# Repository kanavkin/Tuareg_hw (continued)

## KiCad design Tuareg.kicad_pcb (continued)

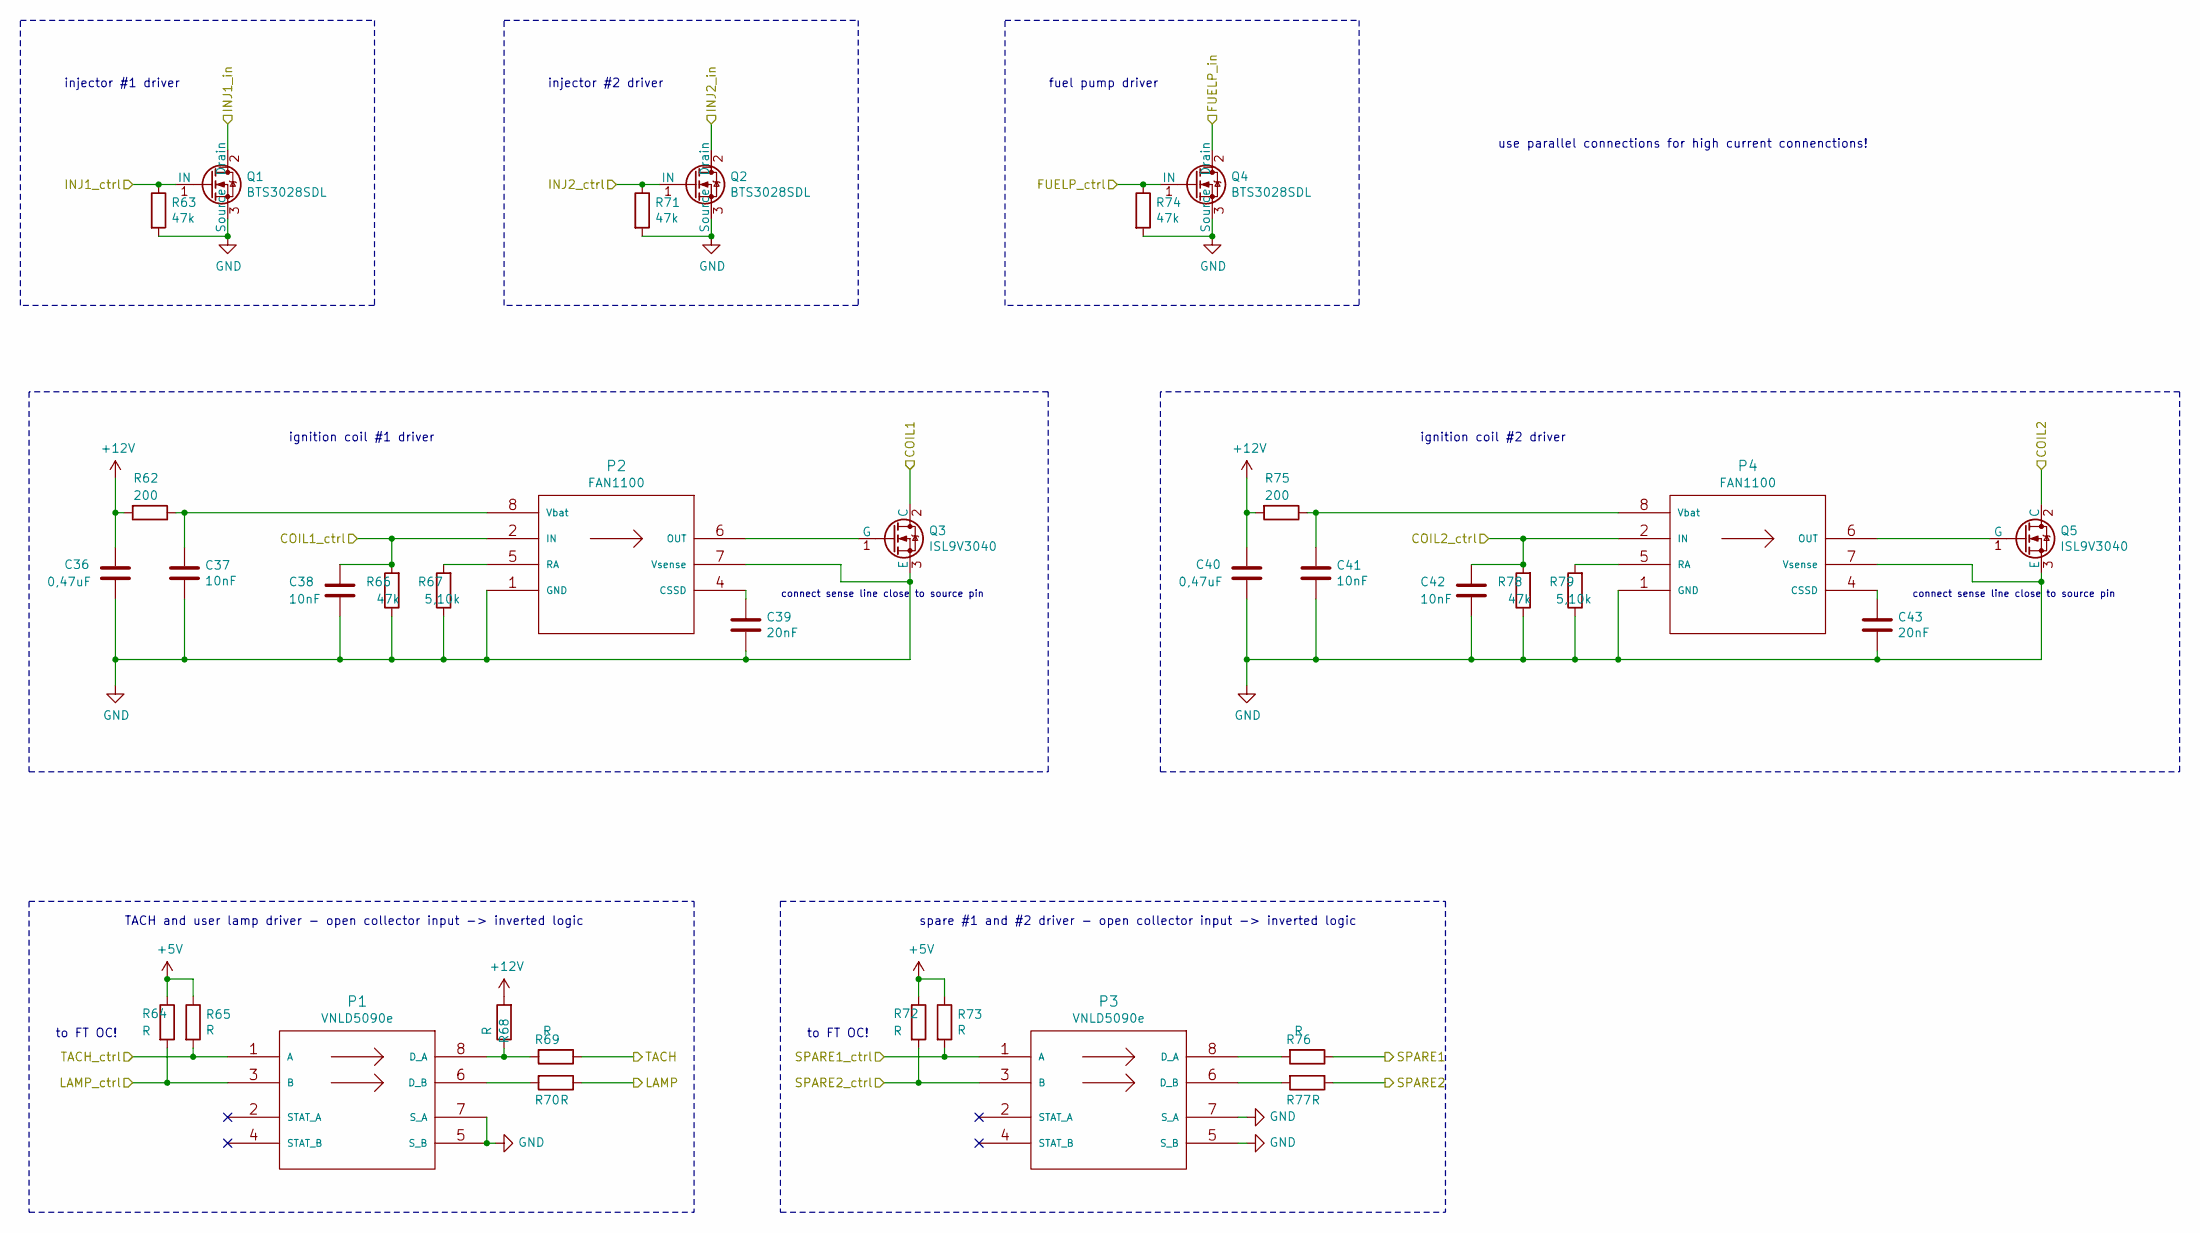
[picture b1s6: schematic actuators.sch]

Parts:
C36, C40: 0,47uF; C_0805_2012Metric
C37, C38, C41, C42: 10nF; C_0805_2012Metric
C39, C43: 20nF; C_0805_2012Metric
P1, P3: VNLD5090e
P2, P4: FAN1100; FAN_1100
Q1, Q2, Q4: BTS3028SDL; BTS3028SD
Q3, Q5: ISL9V3040
R62, R75: 200; R_1206_3216Metric
R63, R66, R71, R74, R78: 47k; R_0805_2012Metric
R64, R65, R68, R69, R70, R72, R73: R; R_0805_2012Metric
R67, R79: 5,10k; R_0805_2012Metric
R76, R77: R; R_1210_3225Metric

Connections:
+5V: R64.1, R65.1, R72.1, R73.1; also elsewhere on the board
+12V: C36.1, C40.1, R62.2, R68.2, R75.2; also elsewhere on the board
/COIL1: C38.1, P2.2 (IN), R66.2; also elsewhere on the board
/COIL2: C42.1, P4.2 (IN), R78.2; also elsewhere on the board
/FUELP: Q4.1 (IN), R74.1; also elsewhere on the board
/INJ1: Q1.1 (IN), R63.1; also elsewhere on the board
/INJ2: Q2.1 (IN), R71.1; also elsewhere on the board
/LAMP: P1.3 (B), R64.2; also elsewhere on the board
/TACH: P1.1 (A), R65.2; also elsewhere on the board
/con_coil1: Q3.2 (C); also elsewhere on the board
/con_coil2: Q5.2 (C); also elsewhere on the board
/con_fuelp: Q4.2 (Drain); also elsewhere on the board
/con_inj1: Q1.2 (Drain); also elsewhere on the board
/con_inj2: Q2.2 (Drain); also elsewhere on the board
/con_lamp: R70.1; also elsewhere on the board
/con_spareact1: R76.1; also elsewhere on the board
/con_spareact2: R77.1; also elsewhere on the board
/con_tach: R69.1; also elsewhere on the board
/spare_act_1: P3.1 (A), R73.2; also elsewhere on the board
/spare_act_2: P3.3 (B), R72.2; also elsewhere on the board
GND: C36.2, C37.2, C38.2, C39.2, C40.2, C41.2, C42.2, C43.2, P1.5 (S_B), P1.7 (S_A), P2.1 (GND), P2.7 (Vsense), P3.5 (S_B), P3.7 (S_A), P4.1 (GND), P4.7 (Vsense), Q1.3 (Source), Q2.3 (Source), Q3.3 (E), Q4.3 (Source), Q5.3 (E), R63.2, R66.1, R67.1, R71.2, R74.2, R78.1, R79.1; also elsewhere on the board
unnamed: C37.1, P2.8 (Vbat), R62.1
unnamed: C39.1, P2.4 (CSSD)
unnamed: C41.1, P4.8 (Vbat), R75.1
unnamed: C43.1, P4.4 (CSSD)
unnamed: P1.6 (D_B), R70.2
unnamed: P1.8 (D_A), R68.1, R69.2
unnamed: P2.5 (RA), R67.2
unnamed: P2.6 (OUT), Q3.1 (G)
unnamed: P3.6 (D_B), R77.2
unnamed: P3.8 (D_A), R76.2
unnamed: P4.5 (RA), R79.2
unnamed: P4.6 (OUT), Q5.1 (G)

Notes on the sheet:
injector #1 driver
injector #2 driver
fuel pump driver
ignition coil #1 driver
to FT OC!
TACH and user lamp driver - open collector input -> inverted logic
spare #1 and #2 driver - open collector input -> inverted logic
connect sense line close to source pin
ignition coil #2 driver
use parallel connections for high current connenctions!

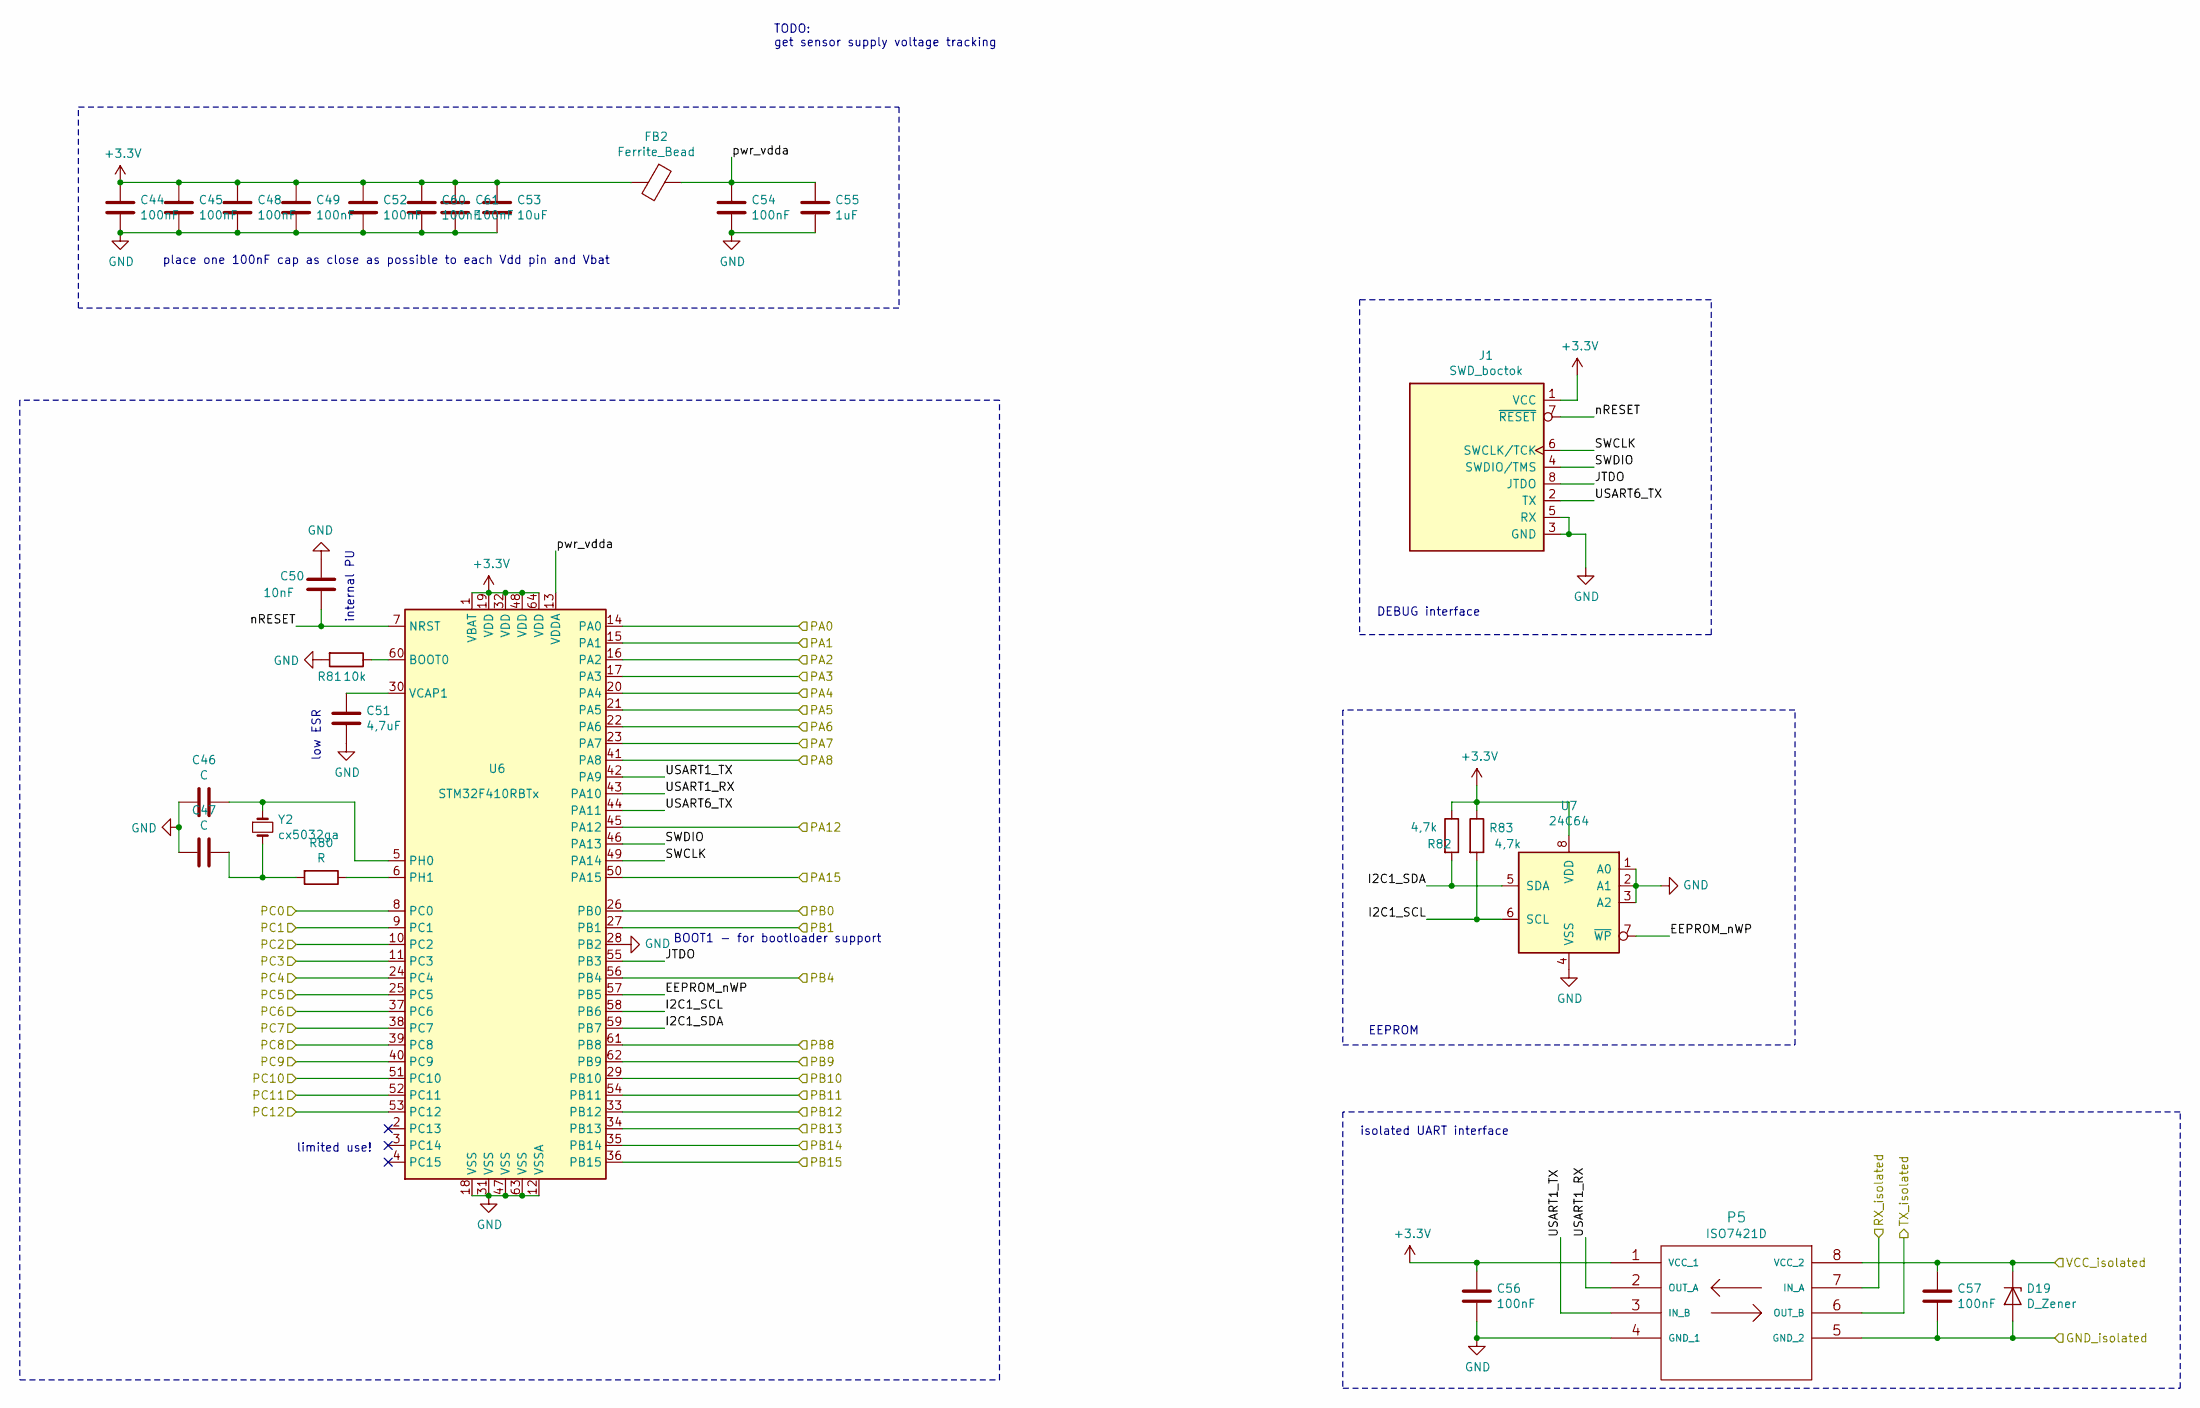
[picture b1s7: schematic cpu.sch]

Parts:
C44, C45, C48, C49, C52, C54, C56, C57, C60, C61: 100nF; C_0805_2012Metric
C46, C47: C; C_0805_2012Metric
C50: 10nF; C_0805_2012Metric
C51: 4,7uF; C_0805_2012Metric
C53: 10uF; C_1206_3216Metric
C55: 1uF; C_0805_2012Metric
D19: D_Zener; D_MELF
FB2: Ferrite_Bead; L_0805_2012Metric
J1: SWD_boctok; swd_boctok
P5: ISO7421D
R80: R; R_0805_2012Metric
R81: 10k; R_0805_2012Metric
R82, R83: 4,7k; R_0805_2012Metric
U6: STM32F410RBTx; LQFP-64_10x10mm_P0.5mm
U7: 24C64
Y2: cx5032ga; cx5032

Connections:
+3V3: C44.1, C45.1, C48.1, C49.1, C52.1, C53.1, C56.1, C60.1, C61.1, FB2.2, J1.1 (VCC), P5.1 (VCC_1), R82.1, R83.1, U6.1 (VBAT), U6.19 (VDD), U6.32 (VDD), U6.48 (VDD), U6.64 (VDD), U7.8 (VDD); also elsewhere on the board
/COIL1: U6.37 (PC6); also elsewhere on the board
/COIL2: U6.38 (PC7); also elsewhere on the board
/FUELP: U6.51 (PC10); also elsewhere on the board
/INJ1: U6.39 (PC8); also elsewhere on the board
/INJ2: U6.40 (PC9); also elsewhere on the board
/LAMP: U6.53 (PC12); also elsewhere on the board
/TACH: U6.52 (PC11); also elsewhere on the board
/ach1: U6.17 (PA3); also elsewhere on the board
/ach2: U6.16 (PA2); also elsewhere on the board
/ach3: U6.15 (PA1); also elsewhere on the board
/ach4: U6.14 (PA0); also elsewhere on the board
/ach5: U6.24 (PC4); also elsewhere on the board
/ach6: U6.23 (PA7); also elsewhere on the board
/ach8: U6.20 (PA4); also elsewhere on the board
/bat: U6.21 (PA5); also elsewhere on the board
/cam: U6.27 (PB1); also elsewhere on the board
/con_gndi: C57.2, D19.2 (A), P5.5 (GND_2); also elsewhere on the board
/con_rx: P5.7 (IN_A); also elsewhere on the board
/con_tx: P5.6 (OUT_B); also elsewhere on the board
/con_vcci: C57.1, D19.1 (K), P5.8 (VCC_2); also elsewhere on the board
/cpu/EEPROM_nWP: U6.57 (PB5), U7.7 (~WP~)
/cpu/I2C1_SCL: R83.2, U6.58 (PB6), U7.6 (SCL)
/cpu/I2C1_SDA: R82.2, U6.59 (PB7), U7.5 (SDA)
/cpu/JTDO: J1.8 (JTDO), U6.55 (PB3)
/cpu/PA8: U6.41 (PA8)
/cpu/PA12: U6.45 (PA12)
/cpu/PA15: U6.50 (PA15)
/cpu/PB10: U6.29 (PB10)
/cpu/PC1: U6.9 (PC1)
/cpu/SWCLK: J1.6 (SWCLK/TCK), U6.49 (PA14)
/cpu/SWDIO: J1.4 (SWDIO/TMS), U6.46 (PA13)
/cpu/USART1_RX: P5.2 (OUT_A), U6.43 (PA10)
/cpu/USART1_TX: P5.3 (IN_B), U6.42 (PA9)
/cpu/USART6_TX: J1.2 (TX), U6.44 (PA11)
/cpu/nRESET: C50.2, J1.7 (~RESET~), U6.7 (NRST)
/cpu/pwr_vdda: C54.1, C55.1, FB2.1, U6.13 (VDDA); also elsewhere on the board
/crank: U6.26 (PB0); also elsewhere on the board
/crash: U6.11 (PC3); also elsewhere on the board
/debug: U6.25 (PC5); also elsewhere on the board
/din_spare1: U6.8 (PC0); also elsewhere on the board
/din_spare2: U6.56 (PB4); also elsewhere on the board
/knock: U6.22 (PA6); also elsewhere on the board
/knock_cs: U6.33 (PB12); also elsewhere on the board
/knock_int: U6.54 (PB11); also elsewhere on the board
/knock_miso: U6.35 (PB14); also elsewhere on the board
/knock_mosi: U6.36 (PB15); also elsewhere on the board
/knock_sck: U6.34 (PB13); also elsewhere on the board
/run: U6.10 (PC2); also elsewhere on the board
/spare_act_1: U6.61 (PB8); also elsewhere on the board
/spare_act_2: U6.62 (PB9); also elsewhere on the board
GND: C44.2, C45.2, C46.2, C47.2, C48.2, C49.2, C50.1, C51.2, C52.2, C53.2, C54.2, C55.2, C56.2, C60.2, C61.2, J1.3 (GND), J1.5 (RX), P5.4 (GND_1), R81.2, U6.12 (VSSA), U6.18 (VSS), U6.28 (PB2), U6.31 (VSS), U6.47 (VSS), U6.63 (VSS), U7.1 (A0), U7.2 (A1), U7.3 (A2), U7.4 (VSS); also elsewhere on the board
unnamed: C46.1, U6.5 (PH0), Y2.1
unnamed: C47.1, R80.2, Y2.2
unnamed: C51.1, U6.30 (VCAP1)
unnamed: R80.1, U6.6 (PH1)
unnamed: R81.1, U6.60 (BOOT0)

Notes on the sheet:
place one 100nF cap as close as possible to each Vdd pin and Vbat
low ESR
internal PU
EEPROM
DEBUG interface
isolated UART interface
BOOT1 - for bootloader support
limited use!
TODO: get sensor supply voltage tracking

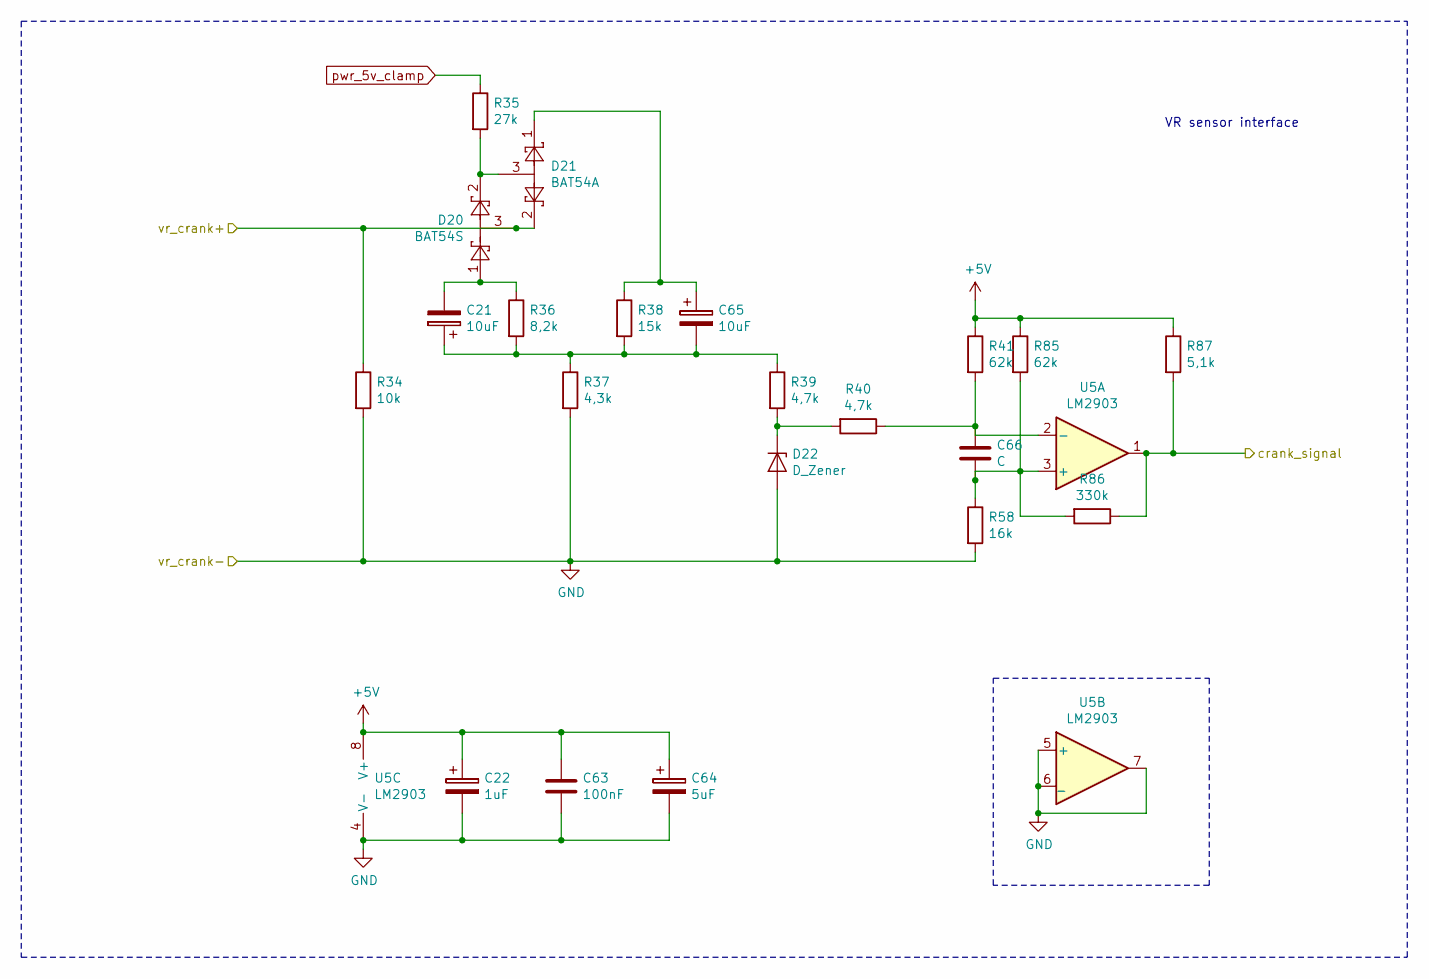
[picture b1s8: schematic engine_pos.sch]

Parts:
C21, C65: 10uF; CP_EIA-7343-31_Kemet-D
C22: 1uF; C_1206_3216Metric
C63: 100nF; C_0805_2012Metric
C64: 5uF; C_1206_3216Metric
C66: C; C_0805_2012Metric
D20: BAT54S; SOT-23
D21: BAT54A; SOT-23
D22: D_Zener; D_MiniMELF
R34: 10k; R_1206_3216Metric
R35: 27k; R_0805_2012Metric
R36: 8,2k; R_0805_2012Metric
R37: 4,3k; R_0805_2012Metric
R38: 15k; R_0805_2012Metric
R39, R40: 4,7k; R_0805_2012Metric
R41, R85: 62k; R_0805_2012Metric
R58: 16k; R_0805_2012Metric
R86: 330k; R_0805_2012Metric
R87: 5,1k; R_0805_2012Metric
U5: LM2903; SOIC-8_3.9x4.9mm_P1.27mm

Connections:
+5V: C22.1, C63.1, C64.1, R41.1, R85.1, R87.1, U5.8 (V+); also elsewhere on the board
/con_vrcrank+: D20.3, D21.2, R34.1; also elsewhere on the board
/crank: R86.1, R87.2, U5.1; also elsewhere on the board
GND: C22.2, C63.2, C64.2, D22.2 (A), R34.2, R37.2, R58.2, U5.4 (V-), U5.5 (+), U5.6 (_), U5.7; also elsewhere on the board
unnamed: C21.1, C65.2, R36.2, R37.1, R38.2, R39.1
unnamed: C21.2, D20.1, R36.1
unnamed: C65.1, D21.1, R38.1
unnamed 113: C66.1, R40.1, R41.2, U5.2 (-); also elsewhere on the board
unnamed: C66.2, R58.1, R85.2, R86.2, U5.3 (+)
unnamed: D20.2, D21.3, R35.2
unnamed: D22.1 (K), R39.2, R40.2
pwr_5v_clamp: R35.1; also elsewhere on the board

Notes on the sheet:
VR sensor interface

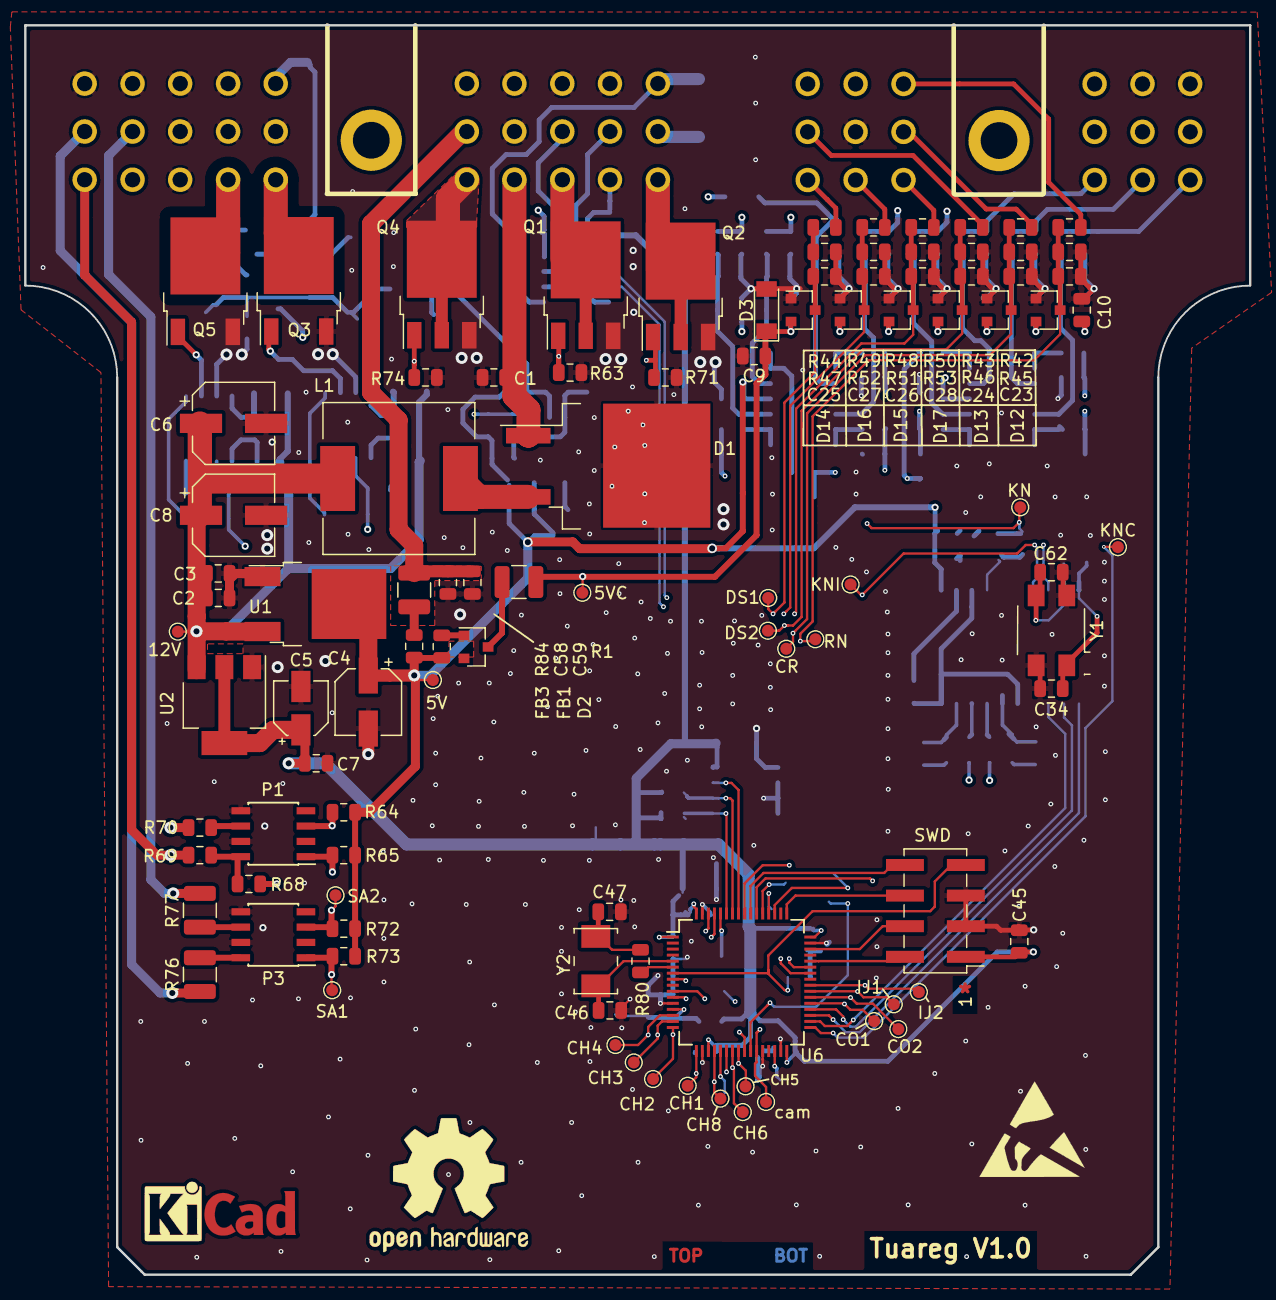
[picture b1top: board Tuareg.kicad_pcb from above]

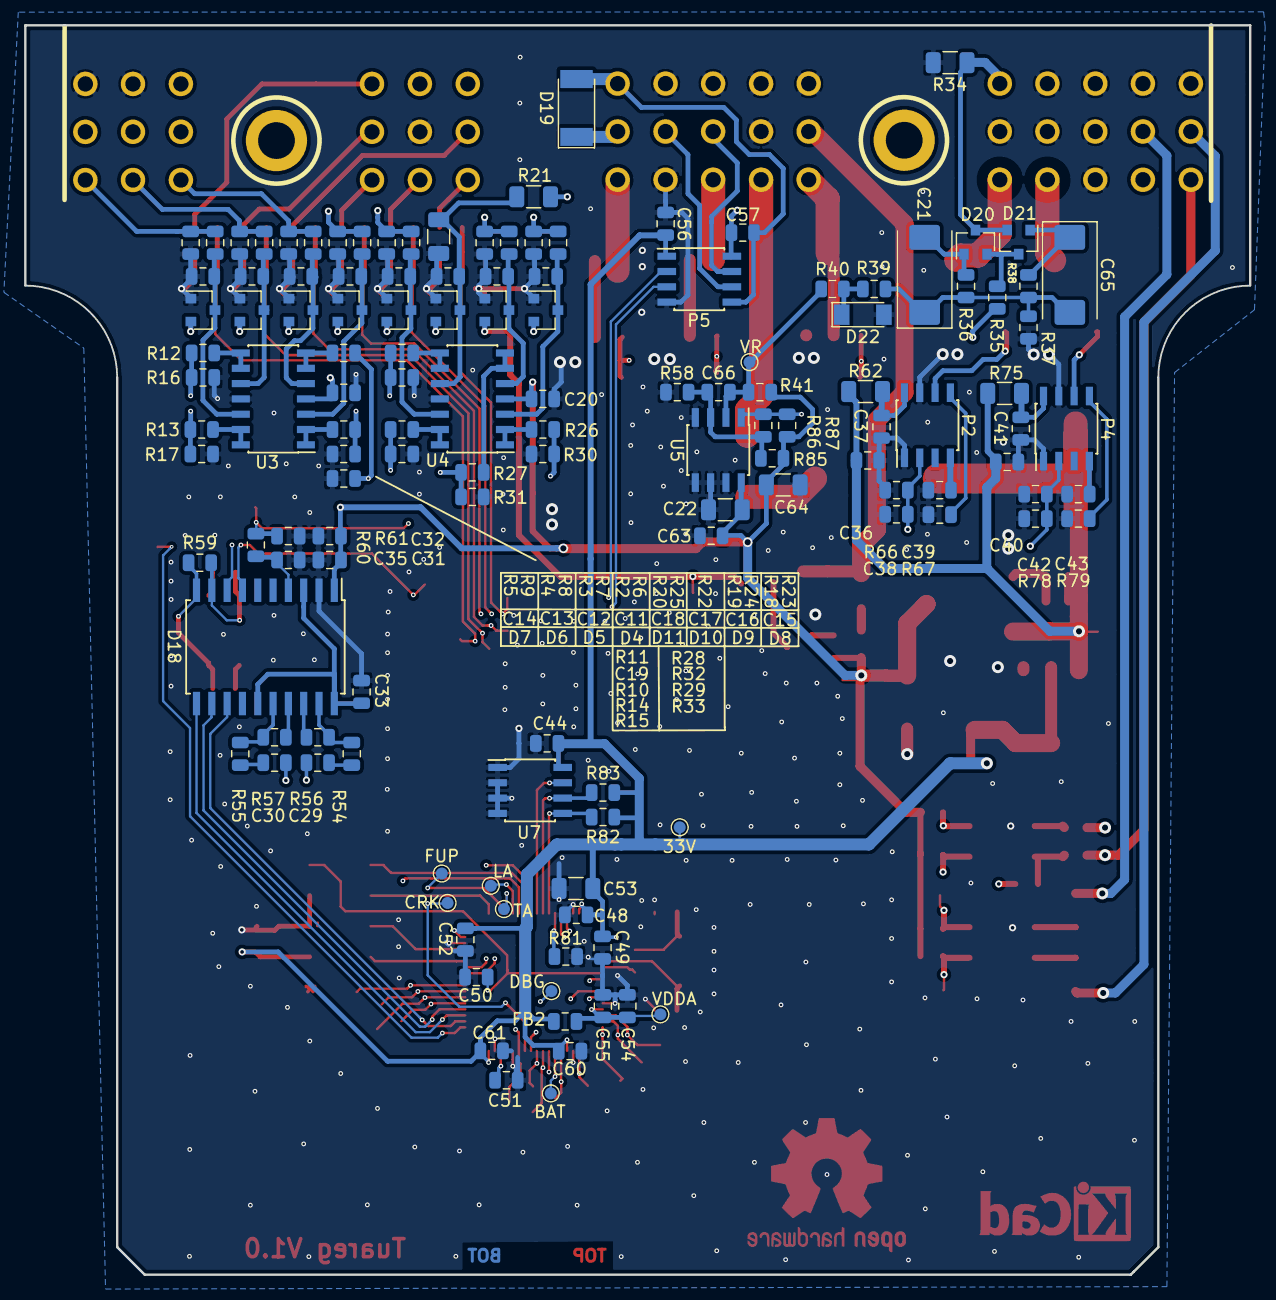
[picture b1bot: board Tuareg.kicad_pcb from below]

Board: 4 copper layers, 101.6 x 103.6 mm, 233 parts (133 on the bottom side), 131 nets.

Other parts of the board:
5V, 5VC, 12V, 33V: TestPoint_Pad_D1.0mm
BAT: TestPoint_Pad_D1.0mm
CH1, CH2, CH3, CH4, CH5, CH6, CH8: TestPoint_Pad_D1.0mm
CO1, CO2: TestPoint_Pad_D1.0mm
CR: TestPoint_Pad_D1.0mm
CRK: TestPoint_Pad_D1.0mm
DBG: TestPoint_Pad_D1.0mm
DS1, DS2: TestPoint_Pad_D1.0mm
FUP: TestPoint_Pad_D1.0mm
IJ1, IJ2: TestPoint_Pad_D1.0mm
KN: TestPoint_Pad_D1.0mm
KNC: TestPoint_Pad_D1.0mm
KNI: TestPoint_Pad_D1.0mm
LA: TestPoint_Pad_D1.0mm
RN: TestPoint_Pad_D1.0mm
SA1, SA2: TestPoint_Pad_D1.0mm
TA: TestPoint_Pad_D1.0mm
VDDA: TestPoint_Pad_D1.0mm
VR: TestPoint_Pad_D1.0mm
cam: TestPoint_Pad_D1.0mm

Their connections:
+3V3: 33V.1; also elsewhere on the board
+5V: 5V.1; also elsewhere on the board
+12V: 12V.1; also elsewhere on the board
/COIL1: CO1.1; also elsewhere on the board
/COIL2: CO2.1; also elsewhere on the board
/FUELP: FUP.1; also elsewhere on the board
/INJ1: IJ1.1; also elsewhere on the board
/INJ2: IJ2.1; also elsewhere on the board
/LAMP: LA.1; also elsewhere on the board
/TACH: TA.1; also elsewhere on the board
/ach1: CH1.1; also elsewhere on the board
/ach2: CH2.1; also elsewhere on the board
/ach3: CH3.1; also elsewhere on the board
/ach4: CH4.1; also elsewhere on the board
/ach5: CH5.1; also elsewhere on the board
/ach6: CH6.1; also elsewhere on the board
/ach8: CH8.1; also elsewhere on the board
/bat: BAT.1; also elsewhere on the board
/cam: cam.1; also elsewhere on the board
/cpu/pwr_vdda: VDDA.1; also elsewhere on the board
/crank: CRK.1; also elsewhere on the board
/crash: CR.1; also elsewhere on the board
/debug: DBG.1; also elsewhere on the board
/din_spare1: DS1.1; also elsewhere on the board
/din_spare2: DS2.1; also elsewhere on the board
/knock: KN.1; also elsewhere on the board
/knock_cs: KNC.1; also elsewhere on the board
/knock_int: KNI.1; also elsewhere on the board
/run: RN.1; also elsewhere on the board
/spare_act_1: SA1.1; also elsewhere on the board
/spare_act_2: SA2.1; also elsewhere on the board
unnamed 113: VR.1; also elsewhere on the board
pwr_5v_clamp: 5VC.1; also elsewhere on the board

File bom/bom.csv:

"Source:","/home/oli/tenere/efi/Tuareg_hw/Tuareg.sch"
"Date:","So 25 Aug 2019 00:06:23 CEST"
"Tool:","Eeschema 5.1.2-f72e74a~84~ubuntu18.04.1"
"Generator:","/usr/share/kicad/plugins/bom_csv_grouped_by_value_with_fp.py"
"Component Count:","200"
"Ref","Qnty","Value","Cmp name","Footprint","Description","Vendor"
"C1, ","1","1uF 50V","C","Capacitor_SMD:C_0805_2012Metric","Unpolarized capacitor",""
"C3, C2, C10, C59, C33, C35, C44, C45, C48, C49, C52, C54, C56, C57, C60, C61, C63, ","17","100nF","C","Capacitor_SMD:C_0805_2012Metric","Unpolarized capacitor",""
"C4, ","1","22uF 16V","CP","Capacitor_SMD:CP_Elec_5x5.8","Polarized capacitor",""
"C5, ","1","22uF 6V","CP","Capacitor_SMD:CP_Elec_4x5.8","Polarized capacitor",""
"C6, ","1","220uF 50V","CP","Capacitor_SMD:CP_Elec_6.3x7.7","Polarized capacitor",""
"C7, ","1","1uF 6V","CP","Capacitor_SMD:C_0805_2012Metric","Polarized capacitor",""
"C8, ","1","22uF 50V","CP","Capacitor_SMD:CP_Elec_6.3x7.7","Polarized capacitor",""
"C9, C58, C11, C12, C13, C14, C15, C16, C17, C18, C23, C24, C25, C26, C27, C28, C55, ","17","1uF","C","Capacitor_SMD:C_0805_2012Metric","Unpolarized capacitor",""
"C19, C20, C32, ","3","0.1uF","C","Capacitor_SMD:C_0805_2012Metric","Unpolarized capacitor",""
"C22, ","1","1uF","CP","Capacitor_SMD:C_1206_3216Metric","Polarized capacitor",""
"C29, C30, ","2","3300pF","C","Capacitor_SMD:C_0805_2012Metric","Unpolarized capacitor",""
"C31, ","1","4.7uF","C","Capacitor_SMD:C_0805_2012Metric","Unpolarized capacitor",""
"C34, C62, ","2","470pF","C","Capacitor_SMD:C_0805_2012Metric","Unpolarized capacitor",""
"C36, C40, ","2","0,47uF","C","Capacitor_SMD:C_0805_2012Metric","Unpolarized capacitor",""
"C37, C38, C41, C42, C50, ","5","10nF","C","Capacitor_SMD:C_0805_2012Metric","Unpolarized capacitor",""
"C39, C43, ","2","20nF","C","Capacitor_SMD:C_0805_2012Metric","Unpolarized capacitor",""
"C46, C47, C66, ","3","C","C","Capacitor_SMD:C_0805_2012Metric","Unpolarized capacitor",""
"C51, ","1","4,7uF","C","Capacitor_SMD:C_0805_2012Metric","Unpolarized capacitor",""
"C53, ","1","10uF","C","Capacitor_SMD:C_1206_3216Metric","Unpolarized capacitor",""
"C64, ","1","5uF","CP","Capacitor_SMD:C_1206_3216Metric","Polarized capacitor",""
"C65, C21, ","2","10uF","CP","Capacitor_Tantalum_SMD:CP_EIA-7343-31_Kemet-D","Polarized capacitor",""
"CON1, ","1","ModICE_48","ModICE_48","boctok_footprints:modICE_48","",""
"D1, ","1","RBO40-40G","RBO40-40G","boctok_footprints:RBO40-40G","Bidirectional dual transient-voltage-suppression diode, center on pin 3",""
"D2, ","1","BAT54","BAT54","Diode_SMD:D_SOT-23_ANK","schottky barrier diode",""
"D3, D22, ","2","D_Zener","D_Zener","Diode_SMD:D_MiniMELF","Zener diode",""
"D4, D5, D6, D7, D8, D9, D10, D11, D12, D13, D14, D15, D16, D17, D20, ","15","BAT54S","BAT54S","Package_TO_SOT_SMD:SOT-23","schottky barrier diode",""
"D18, ","1","TPIC8101","TPIC8101","boctok_footprints:TPIC8101","dual knock sensor interface",""
"D19, ","1","D_Zener","D_Zener","Diode_SMD:D_MELF","Zener diode",""
"D21, ","1","BAT54A","BAT54A","Package_TO_SOT_SMD:SOT-23","schottky barrier diode",""
"FB1, FB3, FB2, ","3","Ferrite_Bead","Ferrite_Bead","Inductor_SMD:L_0805_2012Metric","Ferrite bead",""
"J1, ","1","SWD_boctok","SWD_boctok","boctok_footprints:swd_boctok","Cortex Debug Connector, standard ARM Cortex-M SWD and JTAG interface",""
"L1, ","1","SRR1210A-680M","SRR1210A","boctok_footprints:SRR1210A","Inductor",""
"P1, P3, ","2","VNLD5090e","VNLD5090e","boctok_footprints:VNLD5090e","",""
"P2, P4, ","2","FAN1100","FAN1100","boctok_footprints:FAN_1100","ignition IGBT driver",""
"P5, ","1","ISO7421D","ISO7421D","boctok_footprints:ISO7421D","",""
"Q1, Q2, Q4, ","3","BTS3028SDL","BTS3028SDL","boctok_footprints:BTS3028SD","smart low side power switch",""
"Q3, Q5, ","2","ISL9V3040","ISL9V3040","boctok_footprints:ISL9V3040","300mJ, 400V, N-Channel Ignition IGBT",""
"R1, R84, ","2","100","R","Resistor_SMD:R_1210_3225Metric","Resistor",""
"R2, R3, R4, R5, R18, R19, R20, ","7","100K","R","Resistor_SMD:R_0805_2012Metric","Resistor",""
"R6, R7, R8, R9, R23, R24, R25, R42, R43, R44, R48, R49, R50, R60, R61, R81, ","16","10k","R","Resistor_SMD:R_0805_2012Metric","Resistor",""
"R10, R14, R11, R15, R12, R16, R13, R17, R26, R30, R27, R31, R28, R32, R29, R33, ","16","1500 .1%","R","Resistor_SMD:R_0805_2012Metric","Resistor",""
"R21, R22, ","2","R","R","Resistor_SMD:R_1206_3216Metric","Resistor",""
"R34, ","1","10k","R","Resistor_SMD:R_1206_3216Metric","Resistor",""
"R35, ","1","27k","R","Resistor_SMD:R_0805_2012Metric","Resistor",""
"R36, ","1","8,2k","R","Resistor_SMD:R_0805_2012Metric","Resistor",""
"R37, ","1","4,3k","R","Resistor_SMD:R_0805_2012Metric","Resistor",""
"R38, ","1","15k","R","Resistor_SMD:R_0805_2012Metric","Resistor",""
"R41, R85, ","2","62k","R","Resistor_SMD:R_0805_2012Metric","Resistor",""
"R45, R46, R47, R51, R52, R53, ","6","100k","R","Resistor_SMD:R_0805_2012Metric","Resistor",""
"R54, R56, R57, R55, ","4","39k","R","Resistor_SMD:R_0805_2012Metric","Resistor",""
"R58, ","1","16k","R","Resistor_SMD:R_0805_2012Metric","Resistor",""
"R59, ","1","1k","R","Resistor_SMD:R_0805_2012Metric","Resistor",""
"R62, R75, ","2","200","R","Resistor_SMD:R_1206_3216Metric","Resistor",""
"R63, R71, R74, R66, R78, ","5","47k","R","Resistor_SMD:R_0805_2012Metric","Resistor",""
"R64, R65, R69, R70, R68, R72, R73, R80, ","8","R","R","Resistor_SMD:R_0805_2012Metric","Resistor",""
"R67, R79, ","2","5,10k","R","Resistor_SMD:R_0805_2012Metric","Resistor",""
"R76, R77, ","2","R","R","Resistor_SMD:R_1210_3225Metric","Resistor",""
"R82, R83, R39, R40, ","4","4,7k","R","Resistor_SMD:R_0805_2012Metric","Resistor",""
"R86, ","1","330k","R","Resistor_SMD:R_0805_2012Metric","Resistor",""
"R87, ","1","5,1k","R","Resistor_SMD:R_0805_2012Metric","Resistor",""
"U1, ","1","NCV1117DT","NCV1117DT","boctok_footprints:NCV1117DT","1A Low-Dropout Linear Regulator, automotive",""
"U2, ","1","NCV1117ST","NCV1117ST","boctok_footprints:NCV1117ST","1A Low-Dropout Linear Regulator, automotive",""
"U3, U4, ","2","MCP6004","MCP6004","boctok_footprints:MCP6004","Low-Power, Quad-Operational Amplifiers, SOIC-14",""
"U5, ","1","LM2903","LM2903","Package_SO:SOIC-8_3.9x4.9mm_P1.27mm","Low-Power, Low-Offset Voltage, Dual Comparators, DIP-8/SOIC-8/SSOP-8",""
"U6, ","1","STM32F410RBTx","STM32F410RBTx","Package_QFP:LQFP-64_10x10mm_P0.5mm","ARM Cortex-M4 MCU, 128KB flash, 32KB RAM, 100MHz, 1.7-3.6V, 50 GPIO, LQFP-64",""
"U7, ","1","24C64","24C64","boctok_footprints:24C64","64Kb serial FRAM nonvolatile Memory, SOIC-8",""
"Y1, ","1","lfxtal071673","lfxtal071673","boctok_footprints:lfxtal071673","Four pin crystal, GND on pins 2 and 4, small symbol",""
"Y2, ","1","cx5032ga","cx5032ga","boctok_footprints:cx5032","Two pin crystal, small symbol",""

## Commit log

2019-01-18 cleaned repository
2019-01-19 uploaded the local working directory
2019-01-19 not needed
2019-05-22 added denso tndf13 ecu files
2019-06-02 added schematics
2019-06-02 prepared schematics
2019-06-03 working on schematics
2019-06-10 changed to discrete crank vr sensor cirquitry
2019-06-13 added kicad library as submodule
2019-06-19 fixed references to old kicad lib
2019-06-22 migration to kicad 5.1.2
2019-06-22 routing discrete vr interface TODO: route "crank" signal
2019-06-28 routed crank signal
2019-07-09 minor design improvements for first series production
2019-07-20 cleaning up
2019-07-27 running connection check
2019-07-28 cleaning up bottom layer
2019-07-29 cleaning up fab layers
2019-08-15 added aisler design rules, cleaning up
2019-08-21 added test points and cleaning up silk screen
2019-08-21 corrected silk screen and fab layers
2019-08-23 performed final checks for version 1.0 production
2019-08-24 created interacive bom, bom, updated pdf schematics
2019-09-04 working on bom for parts to order
2019-09-06 added missing component values working on BOM
2019-09-09 cleaned BOMs
